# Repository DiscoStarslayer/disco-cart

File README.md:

# V.Smile Disco-Cart
Custom developer cartridge that easily enables the following
- Ability to dump retail cartridges over Serial or to an SD card
- Ability to flash roms over serial or an SD card to built in flash memory
- Booting cartridge on real V.Smile hardware
- Use Teensy to fuzz data + address bus while system is online (WIP)
- "Stealth" switch to disable sense pinout to allow console to boot as if Cartridge was not inserted

## Contents

- [Cartridge](#cartridge)
- [Usage](#usage)
- [Examples](#examples)
    + [Read retail cartridge to local file over serial](#read-retail-cartridge-to-local-file-over-serial)
    + [Dump retail cartridge to SD card](#dump-retail-cartridge-to-sd-card)
    + [Flash local rom to flashcart](#flash-local-rom-to-flashcart)
- [Args](#args)
    + [`port`](#-port-)
    + [`out`](#-out-)
    + [`limit`](#-limit-)
    + [`bank`](#-bank-)
    + [`mode`](#-mode-)
    + [`name`](#-name-)
    + [`length`](#-length-)
- [Contributing](#contributing)

## Cartridge

## Usage

1. Install [PlatformIO](https://platformio.org/) onto your local system.
2. Install latest LTS for [NodeJS](https://nodejs.org/en/) onto your local system.
3. Install supporting packages for serial management script: 
```shell
cd ./manager
yarn
```
4. Use PlatformIO to pull in required packages, build, and then deploy firmware onto your Teensy (optionally, flash [`firmware.hex`](https://github.com/DiscoStarslayer/vsmile-dumper/releases/download/v0.1/firmware.hex))
5. Socket Teensy into Disco-Cart, ensure USB port on teensy lines up with the USB silkscreen on the board
6. Move mode select switch to the desired position

- `Left`: Cart mode, to insert into a V-Smile and boot a flashed rom
- `Middle`: Flash mode, select this mode to read/write to the internal flash on the Disco-Cart
- `Right`: Dump mode, select this mode to read/write from an inserted retail cartridge
7. Use manager scripts to perform your desired action

## Examples

### Read retail cartridge to local file over serial

```shell
# Switch: Dump mode
node .\index.js --port=COM3 --out=./thomas.bin --limit=3FFFFF --bank=LOW
```

### Dump retail cartridge to SD card

```shell
# Switch: Dump mode
node .\index.js --port=COM3 --mode=sddump --name=thomas.bin --length=3FFFFF
```

### Flash local rom to flashcart

```shell
# Switch: Write mode
node .\index.js --port=COM3 --mode=write --rom=./thomas.bin
```

### Inserting into a V.Smile
Ensure mode select switch is in Cart mode. Teensy can remain inserted in cartridge while in this mode. If you wish to write a new flash, you can do so while the cartridge is inserted by first switching mode to Write mode and running the write action from the manager

## Args

### `port`

Determines the serial port to connect to, defaults to `COM3` for Windows or `/dev/ttyACM0` for Linux.

### `out`

Relative file path to write the rom dump to, defaults to `./dump.bin`

### `limit`

Max address to dump to in hex. Banked cartridges generally have a 4MB and 2MB flash, so they need a limit of `1FFFFF` and `FFFFF` respectively. A single 8MB flash should accept `3FFFFF`.

### `bank`

If cartridge is banked, select which bank to dump. Defaults to `LOW`, non-banked cartridges should be set to `LOW`.

### `mode`

Which mode to operate the teensy in. Accepts `dump`, `write` and `sddump`.

### `name`

When writing to SD card, the file name to write to

### `length`

When writing to SD card, the size of the file to be written, in hex.

## Contributing

Project is fully open source under GPL3, including hardware design.
- `cartridge`: Hardware design as a KiCad Project
- `manager`: JS Script to aid with interfacing the Teensy over serial
- `src`: C++ Platform IO source for Teensy 4.1

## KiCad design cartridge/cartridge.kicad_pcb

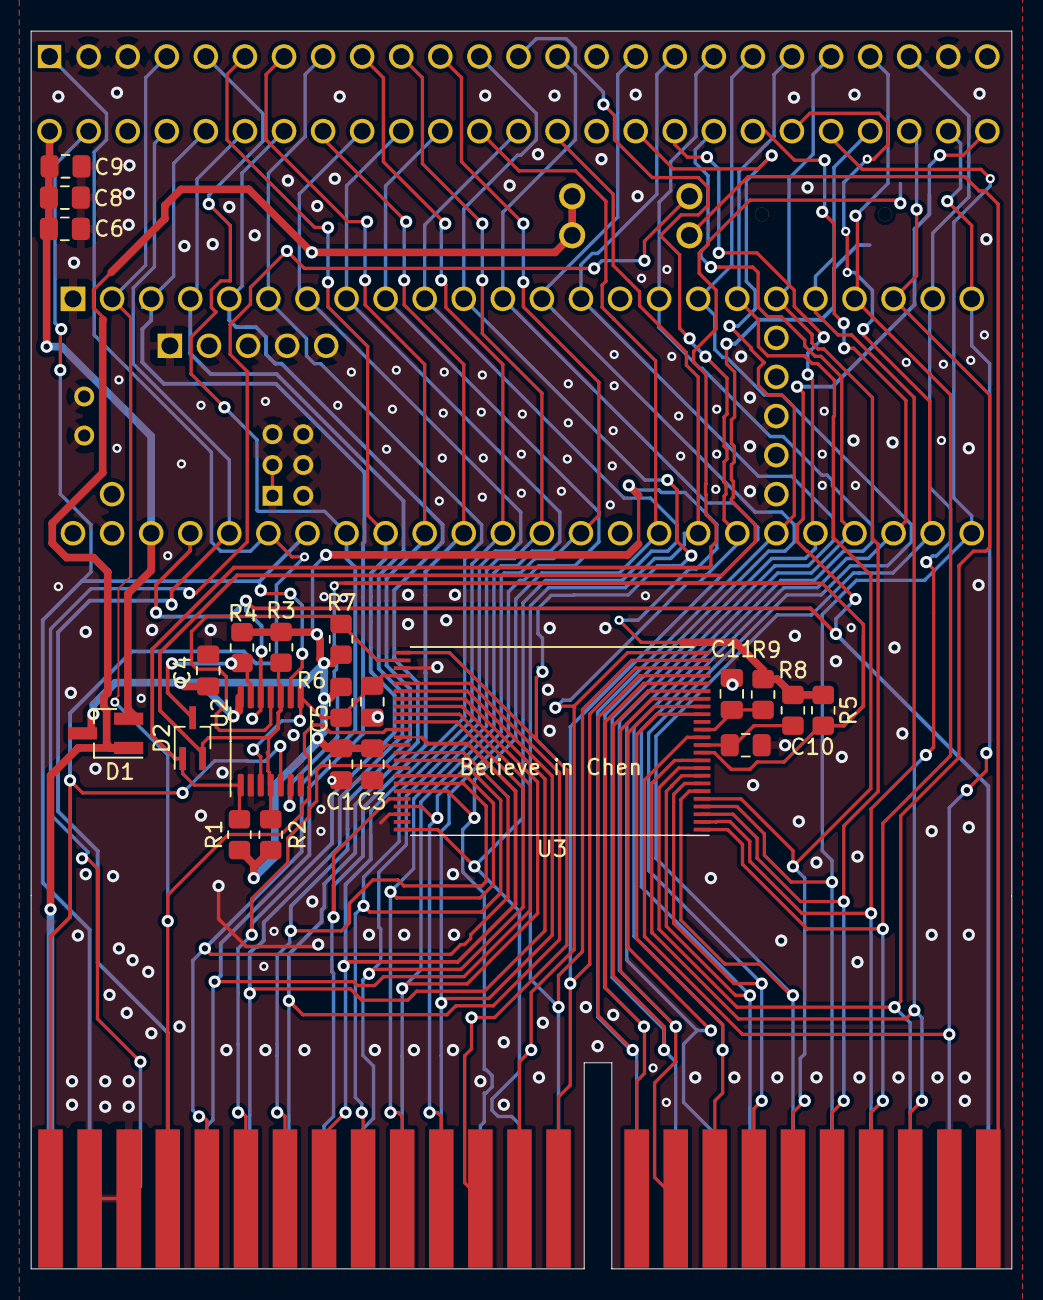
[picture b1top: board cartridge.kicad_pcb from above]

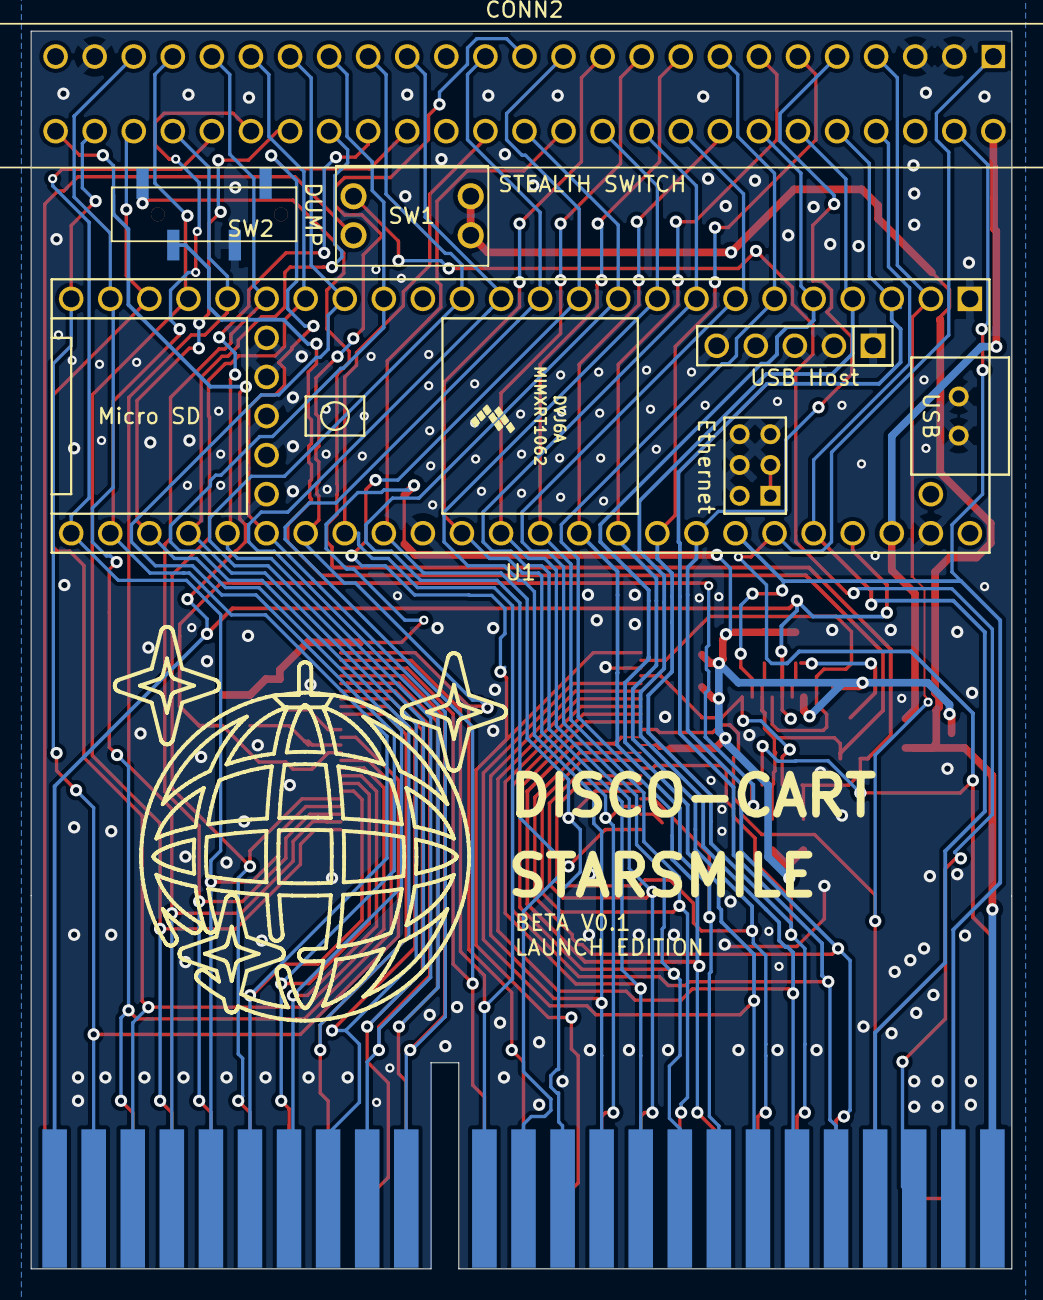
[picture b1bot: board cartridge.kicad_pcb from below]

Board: 2 copper layers, 63.7 x 80.5 mm, 28 parts (4 on the bottom side), 40 nets.

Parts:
C1, C8: 1uF; C_0805_2012Metric_Pad1.18x1.45mm_HandSolder
C3, C4, C5, C9, C10, C11: 0.1uF; C_0805_2012Metric_Pad1.18x1.45mm_HandSolder
C6: 10uF; C_0805_2012Metric_Pad1.18x1.45mm_HandSolder
CONN1: Conn_Cartridge; Connector_Cartridge
CONN2: 5530843-5
D1: PMEG2005CT; SOT-23_Handsoldering
D2: MMBD717LT1G‎; SOT-323_SC-70_Handsoldering
DISCO-CART: logo
R1, R2, R3, R4, R5, R6, R7, R8, R9: 10k; R_0805_2012Metric_Pad1.20x1.40mm_HandSolder
SW1: DS01-254-S-02BE
SW2: CL-SB-13B-01T‎; CL-SB-13B-01T
U1: Teensy4.1; Teensy41
U2: SN74CBTLV3125PW; TSSOP-14_4.4x5mm_P0.65mm
U3: SST39VF6401B; TSOP-I-48_18.4x12mm_P0.5mm

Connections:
/1OE: D2.1 (K), R1.2, SW2.1, U2.1 (1OE)
/2OE: D2.2 (K), R2.2, R3.2, SW2.2, U2.4 (2OE), U2.10 (3OE)
/3V3: C6.1, C8.1, C9.1, CONN2.26, D1.2 (A), U1.46 (3V3)
/4OE: D2.3 (A), R4.2, U2.13 (4OE)
/A0: CONN1.12, CONN1.31, CONN2.12, CONN2.32, U1.5 (3_LRCLK2), U1.11 (9_OUT1C), U3.25 (A0), U3.29 (D0)
/A1: CONN1.13, CONN1.30, CONN2.13, CONN2.31, U1.4 (2_OUT2), U1.31 (39_MISO1_OUT1A), U3.24 (A1), U3.31 (D1)
/A2: CONN1.29, CONN1.38, CONN2.30, CONN2.39, U1.3 (1_TX1_CTX2_MISO1), U1.32 (40_A16), U3.23 (A2), U3.33 (D2)
/A3: CONN1.4, CONN1.14, CONN2.4, CONN2.14, U1.2 (0_RX1_CRX2_CS1), U1.12 (10_CS_MQSR), U3.22 (A3), U3.35 (D3)
/A4: CONN1.5, CONN1.39, CONN2.5, CONN2.41, U1.30 (38_CS1_IN1), U1.41 (19_A5_SCL), U3.21 (A4), U3.38 (D4)
/A5: CONN1.6, CONN1.15, CONN2.6, CONN2.16, U1.13 (11_MOSI_CTX1), U1.40 (18_A4_SDA), U3.20 (A5), U3.40 (D5)
/A6: CONN1.7, CONN1.40, CONN2.7, CONN2.42, U1.29 (37_CS), U1.39 (17_A3_TX4_SDA1), U3.19 (A6), U3.42 (D6)
/A7: CONN1.16, CONN1.32, CONN2.17, CONN2.33, U1.14 (12_MISO_MQSL), U1.38 (16_A2_RX4_SCL1), U3.18 (A7), U3.44 (D7)
/A8: CONN1.35, CONN1.42, CONN2.36, CONN2.44, U1.9 (7_RX2_OUT1A), U1.27 (35_TX8), U3.8 (A8), U3.30 (D8)
/A9: CONN1.18, CONN1.34, CONN2.19, CONN2.35, U1.8 (6_OUT1D), U1.17 (25_A11_RX6_SDA2), U3.7 (A9), U3.32 (D9)
/A10: CONN1.33, CONN1.43, CONN2.34, CONN2.45, U1.7 (5_IN2), U1.26 (34_RX8), U3.6 (A10), U3.34 (D10)
/A11: CONN1.8, CONN1.19, CONN2.8, CONN2.20, U1.6 (4_BCLK2), U1.18 (26_A12_MOSI1), U3.5 (A11), U3.36 (D11)
/A12: CONN1.9, CONN1.44, CONN2.9, CONN2.46, U1.25 (33_MCLK2), U1.37 (15_A1_RX3_SPDIF_IN), U3.4 (A12), U3.39 (D12)
/A13: CONN1.10, CONN1.20, CONN2.10, CONN2.21, U1.19 (27_A13_SCK1), U1.36 (14_A0_TX3_SPDIF_OUT), U3.3 (A13), U3.41 (D13)
/A14: CONN1.36, CONN1.45, CONN2.37, CONN2.47, U1.20 (28_RX7), U1.33 (41_A17), U3.2 (A14), U3.43 (D14)
/A15: CONN1.11, CONN1.21, CONN2.11, CONN2.22, U1.21 (29_TX7), U1.35 (13_SCK_LED), U3.1 (A15), U3.45 (D15)
/A16: CONN1.37, CONN2.38, U1.10 (8_TX2_IN1), U3.48 (A16)
/A17: CONN1.41, CONN2.43, U1.28 (36_CS), U3.17 (A17)
/A18: CONN1.17, CONN2.18, U1.16 (24_A10_TX6_SCL2), U3.16 (A18)
/A19: CONN1.46, CONN2.48, U1.22 (30_CRX3), U3.9 (A19)
/A20: CONN1.22, CONN2.23, U1.23 (31_CTX3), U3.10 (A20)
/A21: CONN1.47, CONN2.49, U1.24 (32_OUT1B), U3.13 (A21)
/CE#: R7.2, U2.11 (4B), U3.26 (CE#)
/EXT_CART: CONN1.24, SW1.3
/OE#: C5.2, R6.2, U2.3 (1B), U2.8 (3B), U3.28 (OE#)
/RAM_CSB: CONN1.26, CONN2.27, U1.42 (20_A6_TX5_LRCLK1), U2.9 (3A)
/RAM_RWB: CONN1.1, CONN2.1, U1.43 (21_A7_RX5_BCLK1), U2.5 (2A)
/ROM0_1: CONN1.48, CONN2.50, U1.45 (23_A9_CRX1_MCLK1), U2.12 (4A)
/ROM_CSB2: CONN1.28, CONN2.29, U1.44 (22_A8_CTX1)
/RST#: C10.2, R8.2, U3.12 (RST#)
/SENSE: CONN1.27, SW1.4
/VCC: C1.1, C3.1, C4.1, D1.3 (K), R1.1, R2.1, R3.1, R4.1, R5.1, R6.1, R7.1, R8.1, R9.1, U2.14 (VCC), U3.37 (VDD)
/VDD_EXT: CONN1.25, D1.1 (A), SW1.1, SW1.2
/WE#: R5.2, U2.6 (2B), U3.11 (WE#)
/WP#: C11.2, R9.2, U3.14 (WP#)
GND: C1.2, C3.2, C4.2, C5.1, C6.2, C8.2, C9.2, C10.1, C11.1, CONN1.2, CONN1.3, CONN1.23, CONN2.2, CONN2.3, CONN2.24, SW2.3, U1.1 (GND), U1.34 (GND), U1.47 (GND), U1.50 (VBAT), U1.51 (3V3), U1.52 (GND), U1.53 (PROGRAM), U1.54 (ON_OFF), U1.55 (5V), U1.56 (D-), U1.57 (D+), U1.58 (GND), U1.59 (GND), U1.60 (R+), U1.61 (LED), U1.62 (T-), U1.63 (T+), U1.64 (GND), U1.65 (R-), U1.66 (D-), U1.67 (D+), U2.2 (1A), U2.7 (GND), U3.27 (GND), U3.46 (GND)

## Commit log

2020-12-08 Wow, what terrible code has befallen on us this night
2020-12-13 Cleanup main slightly, add command interface
2020-12-13 Add manager script to enable easy cartridge dumping
2020-12-13 Remove IDE leftovers
2020-12-13 License under GPL3
2021-01-03 WIP Schematic
2021-01-08 WIP part layout
2021-01-08 Bus extracted
2021-03-13 DiscoCart V0.1
2021-04-13 Final PCB revision for launch
2021-04-13 WIP Cartridge Dumping PCB (#4)
    Accurate dumping of existing V-Smile Cartridges
    Dumps let us test accuracy of flash cart
    Allow easy dumping of cartridges for end users for backup + preservation (already found an undumped/unknown release)
    Direct Teensy -> VSmile bus connection
    Allows fuzzing of address bus and listening on the data bus. Potentially can be used to dump firmware from blob-top BIOS's
    "Stealth Mode" DIP Switch to allow insertion of cartridge without triggering console detection to aid with bus pirating
2021-08-01 update code with SD card logic, port to new cart design and teensy 4.1 (#5)
2021-08-01 Update readme to reflect new model
2021-08-01 Update readme to reflect new model (#6)
2021-08-01 Formatting
2021-08-01 Formatting and documenting cartridge use
2021-08-01 Use /dev/ttyACM0 as default serial path for Linux
2021-08-01 Use /dev/ttyACM0 as default serial path for Linux (#7)
2021-08-08 Update default serial port documentation
2021-08-12 Hack: Remove sdcard logic
2021-08-22 Update default serial port documentation (#8)
2022-03-06 Update readme to reflect new model (#9)
2022-08-18 Relicense source-code under MIT
    Contribution relicensing signed off by @sp1187
2022-08-18 License hardware under CERN-OHL-P v2
2022-08-18 Relicense source-code under MIT (#10)
    Contribution relicensing signed off by @sp1187
2022-08-18 License hardware under CERN-OHL-P v2 (#11)
2022-08-18 sd: Allow cart to work without SD card inserted
    No reason to make the SD card required, replace Error Halt with Error Print.
2026-02-18 add MPN column and pcbway files
2026-03-02 sd: Allow cart to work without SD card inserted (#12)
    No reason to make the SD card required, replace Error Halt with Error Print.
